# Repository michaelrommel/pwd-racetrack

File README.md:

# pwd-racetrack
A Pinewood Derby racetrack timer and start gate electronics circuits + firmware.

This software implements the firmware for a Pinewood Derby race track
electronics. The race track receives commands, like the setup or start commands
and sends back results, like the finishing times for each lane after a heat ends.

The racetrack electronics in the subdirectory circuits consists of three main parts:
- the main controller based on an Arduino Due with a protoype extension board.
  The extension board implements the connections to the finish line display
  modules and to the start gate.
- the display modules (one per lane) implement the main display of the achieved
  place in the heat and the display of the time in milliseconds. Also the LDR
  (Light Dependent Resistor) needed to detect the interruption of the laser
  beam is implemented on this module.
- the start gate electronics. This part is a separate Arduino Mega 2560
  controlling four RFID readers to detect the cars on each track, four OLED
  displays to shoe the car owner names and the solenoid for opening the start
  gate.

If you commit to this repo, please use descriptive commit messages. A good guide
can be found at: https://chris.beams.io/posts/git-commit/

In short, a properly formed Git commit subject line should always be able to 7
complete the following sentence:

- If applied, this commit will <_your subject line here_>

(c) 2018 by Michael Rommel

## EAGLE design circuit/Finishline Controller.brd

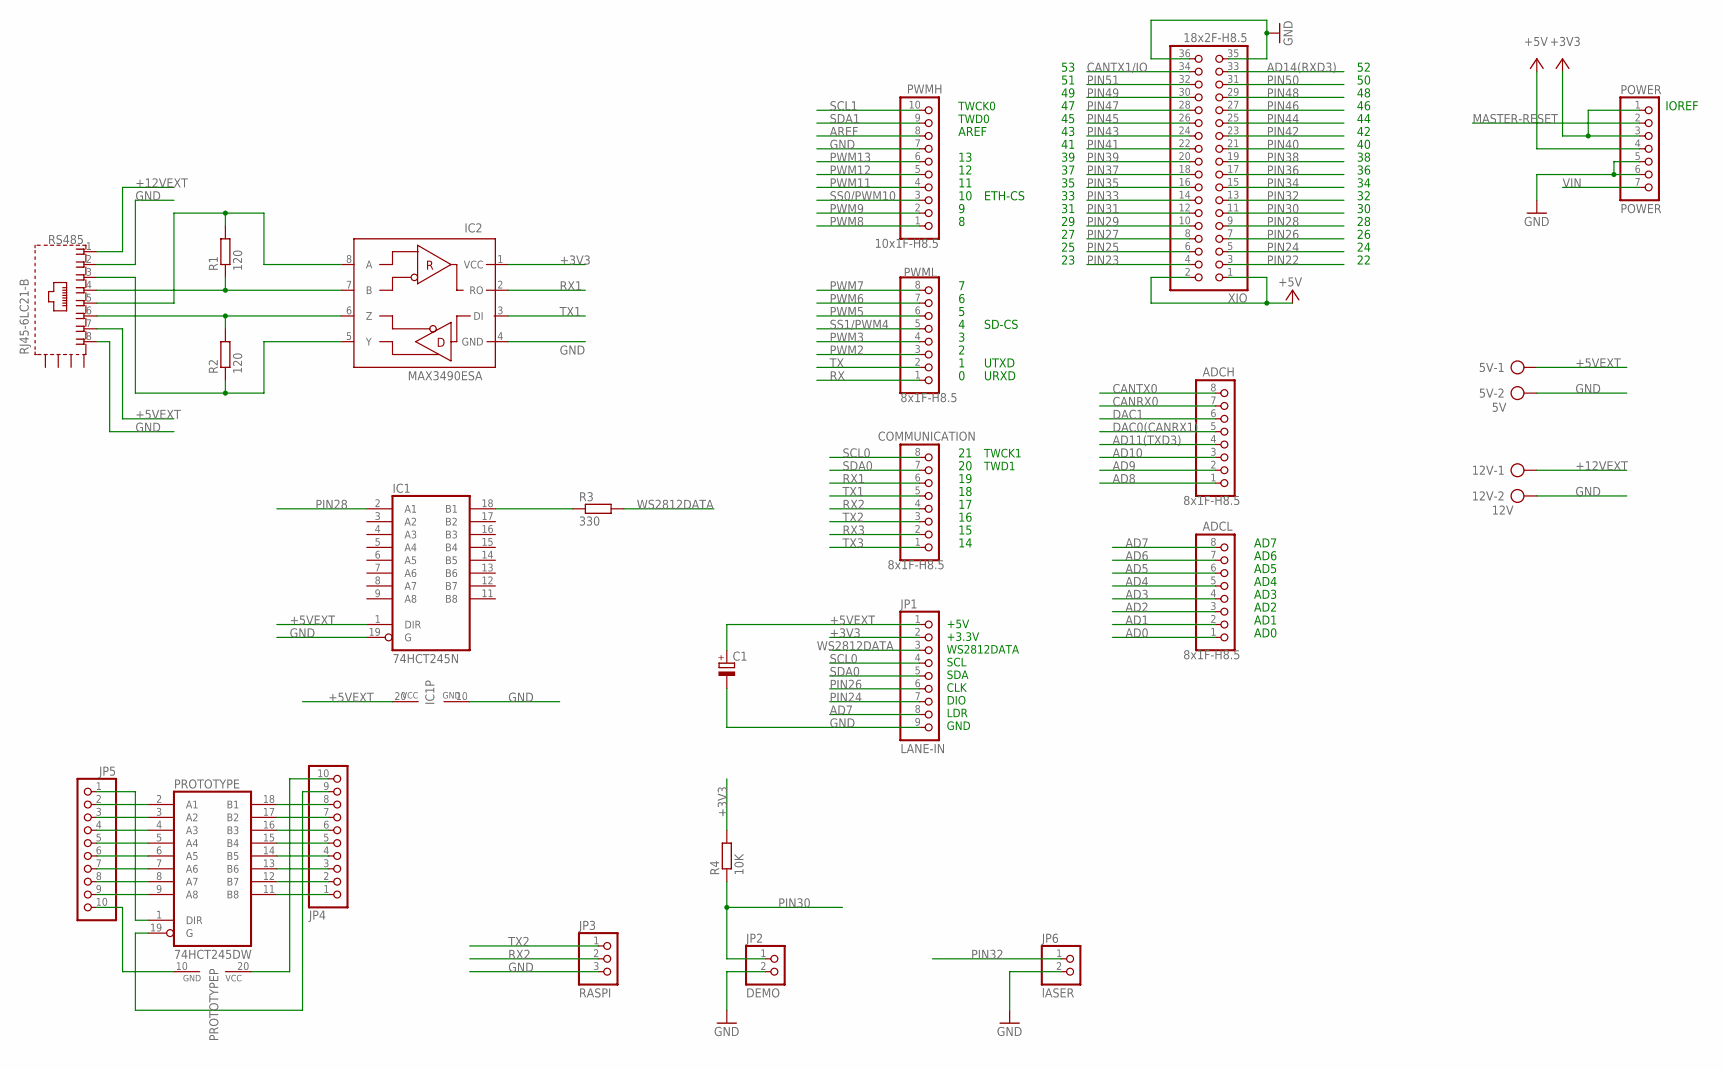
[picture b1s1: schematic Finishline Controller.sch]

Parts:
5V: 5V; AK300/2
12V: 12V; AK300/2
ADCH: 8x1F-H8.5; 1X08
ADCL: 8x1F-H8.5; 1X08
C1: CPOL-EUE5-10.5; E5-10,5
COMMUNICATION: 8x1F-H8.5; 1X08
IC1: 74HCT245N; DIL20
IC2: MAX3490ESA; SO08
JP1: LANE-IN; 1X09
JP2: DEMO; 1X02
JP3: RASPI; 1X03
JP4, JP5: PINHD-1X10; 1X10
JP6: lASER; 1X02
POWER: POWER; 1X07
PROTOTYPE: 74HCT245DW; SO20W
PWMH: 10x1F-H8.5; 1X10
PWML: 8x1F-H8.5; 1X08
R1, R2: 120; R0805
R3: 330; R0805
R4: 10K; R0805
RS485: RJ45-6LC21-B; RJ45-SHIELD1
XIO: 18x2F-H8.5; 2X18

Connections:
+3V3: IC2.1 (VCC), JP1.2, POWER.1, POWER.3, R4.2
+5V: POWER.4, XIO.1, XIO.2
+5VEXT: 5V.1, C1.+, IC1.1 (DIR), IC1.20 (VCC), JP1.1, RS485.7
+12VEXT: 12V.1, RS485.1
AD0: ADCL.1
AD1: ADCL.2
AD2: ADCL.3
AD3: ADCL.4
AD4: ADCL.5
AD5: ADCL.6
AD6: ADCL.7
AD7: ADCL.8, JP1.8
AD8: ADCH.1
AD9: ADCH.2
AD10: ADCH.3
AD11(TXD3): ADCH.4
AD14(RXD3): XIO.33
AREF: PWMH.8
CANRX0: ADCH.7
CANTX0: ADCH.8
CANTX1/IO: XIO.34
DAC0(CANRX1): ADCH.5
DAC1: ADCH.6
GND: 5V.2, 12V.2, C1.-, IC1.10 (GND), IC1.19 (G), IC2.4 (GND), JP1.9, JP2.2, JP3.3, JP6.2, POWER.5, POWER.6, PWMH.7, RS485.2, RS485.8, XIO.35, XIO.36
MASTER-RESET: POWER.2
unnamed: IC1.18 (B1), R3.1
unnamed: IC2.7 (B), R1.1, RS485.4
unnamed: IC2.6 (Z), R2.2, RS485.6
unnamed: IC2.5 (Y), R2.1, RS485.3
unnamed: IC2.8 (A), R1.2, RS485.5
unnamed: JP5.2, PROTOTYPE.2 (A1)
unnamed: JP5.3, PROTOTYPE.3 (A2)
unnamed: JP5.4, PROTOTYPE.4 (A3)
unnamed: JP5.5, PROTOTYPE.5 (A4)
unnamed: JP5.6, PROTOTYPE.6 (A5)
unnamed: JP5.7, PROTOTYPE.7 (A6)
unnamed: JP5.8, PROTOTYPE.8 (A7)
unnamed: JP5.9, PROTOTYPE.9 (A8)
unnamed: JP5.10, PROTOTYPE.10 (GND)
unnamed: JP5.1, PROTOTYPE.1 (DIR)
unnamed: JP4.8, PROTOTYPE.18 (B1)
unnamed: JP4.7, PROTOTYPE.17 (B2)
unnamed: JP4.6, PROTOTYPE.16 (B3)
unnamed: JP4.5, PROTOTYPE.15 (B4)
unnamed: JP4.4, PROTOTYPE.14 (B5)
unnamed: JP4.3, PROTOTYPE.13 (B6)
unnamed: JP4.2, PROTOTYPE.12 (B7)
unnamed: JP4.1, PROTOTYPE.11 (B8)
unnamed: JP4.9, PROTOTYPE.19 (G)
unnamed: JP4.10, PROTOTYPE.20 (VCC)
PIN22: XIO.3
PIN23: XIO.4
PIN24: JP1.7, XIO.5
PIN25: XIO.6
PIN26: JP1.6, XIO.7
PIN27: XIO.8
PIN28: IC1.2 (A1), XIO.9
PIN29: XIO.10
PIN30: JP2.1, R4.1, XIO.11
PIN31: XIO.12
PIN32: JP6.1, XIO.13
PIN33: XIO.14
PIN34: XIO.15
PIN35: XIO.16
PIN36: XIO.17
PIN37: XIO.18
PIN38: XIO.19
PIN39: XIO.20
PIN40: XIO.21
PIN41: XIO.22
PIN42: XIO.23
PIN43: XIO.24
PIN44: XIO.25
PIN45: XIO.26
PIN46: XIO.27
PIN47: XIO.28
PIN48: XIO.29
PIN49: XIO.30
PIN50: XIO.31
PIN51: XIO.32
PWM2: PWML.3
PWM3: PWML.4
PWM5: PWML.6
PWM6: PWML.7
PWM7: PWML.8
PWM8: PWMH.1
PWM9: PWMH.2
PWM11: PWMH.4
PWM12: PWMH.5
PWM13: PWMH.6
RX: PWML.1
RX1: COMMUNICATION.6, IC2.2 (RO)
RX2: COMMUNICATION.4, JP3.2
RX3: COMMUNICATION.2
SCL0: COMMUNICATION.8, JP1.4
SCL1: PWMH.10
SDA0: COMMUNICATION.7, JP1.5
SDA1: PWMH.9
SS0/PWM10: PWMH.3
SS1/PWM4: PWML.5
TX: PWML.2
TX1: COMMUNICATION.5, IC2.3 (DI)
TX2: COMMUNICATION.3, JP3.1
TX3: COMMUNICATION.1
VIN: POWER.7
WS2812DATA: JP1.3, R3.2

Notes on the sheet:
TWCK1
TWD1
IOREF
TWCK0
TWD0
AD1
AD2
AD3
AD4
AD5
AD6
AD0
AREF
AD7
SD-CS
UTXD
URXD
ETH-CS
+5V +3.3V WS2812DATA SCL SDA CLK DIO LDR GND

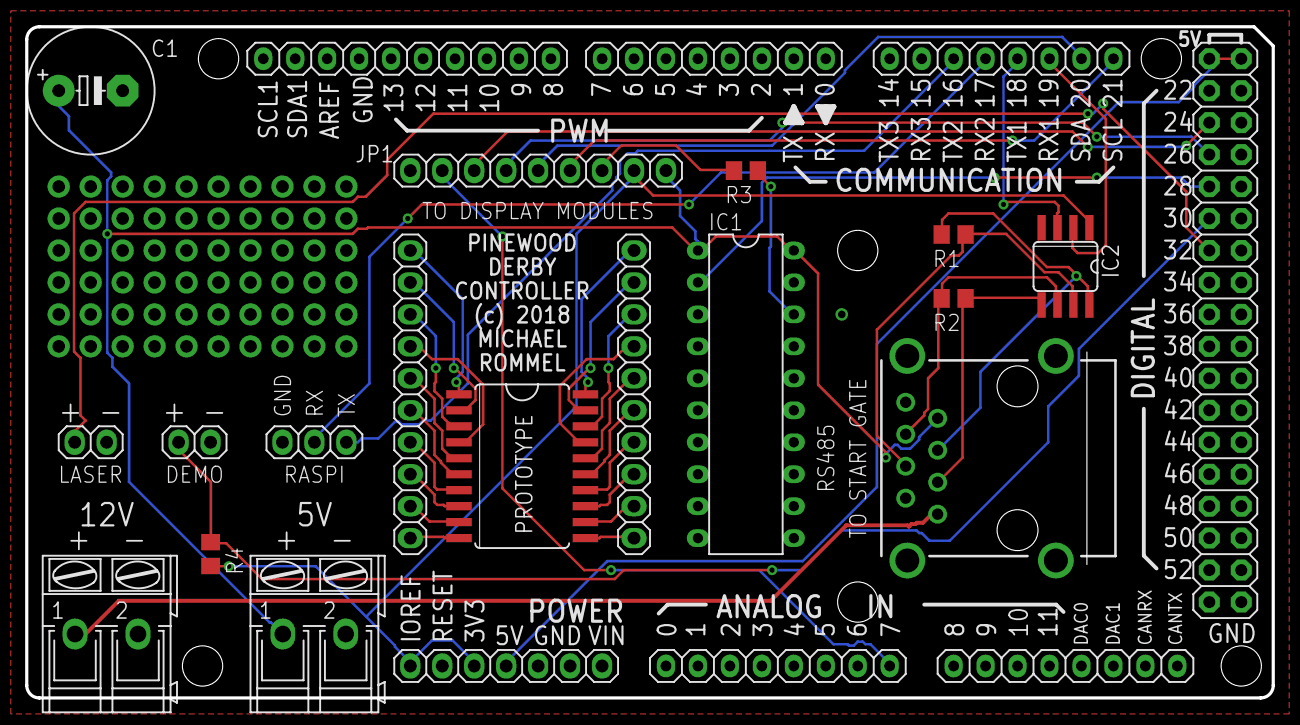
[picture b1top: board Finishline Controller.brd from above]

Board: 2 copper layers, 99.1 x 53.3 mm, 24 parts (0 on the bottom side), 43 nets.

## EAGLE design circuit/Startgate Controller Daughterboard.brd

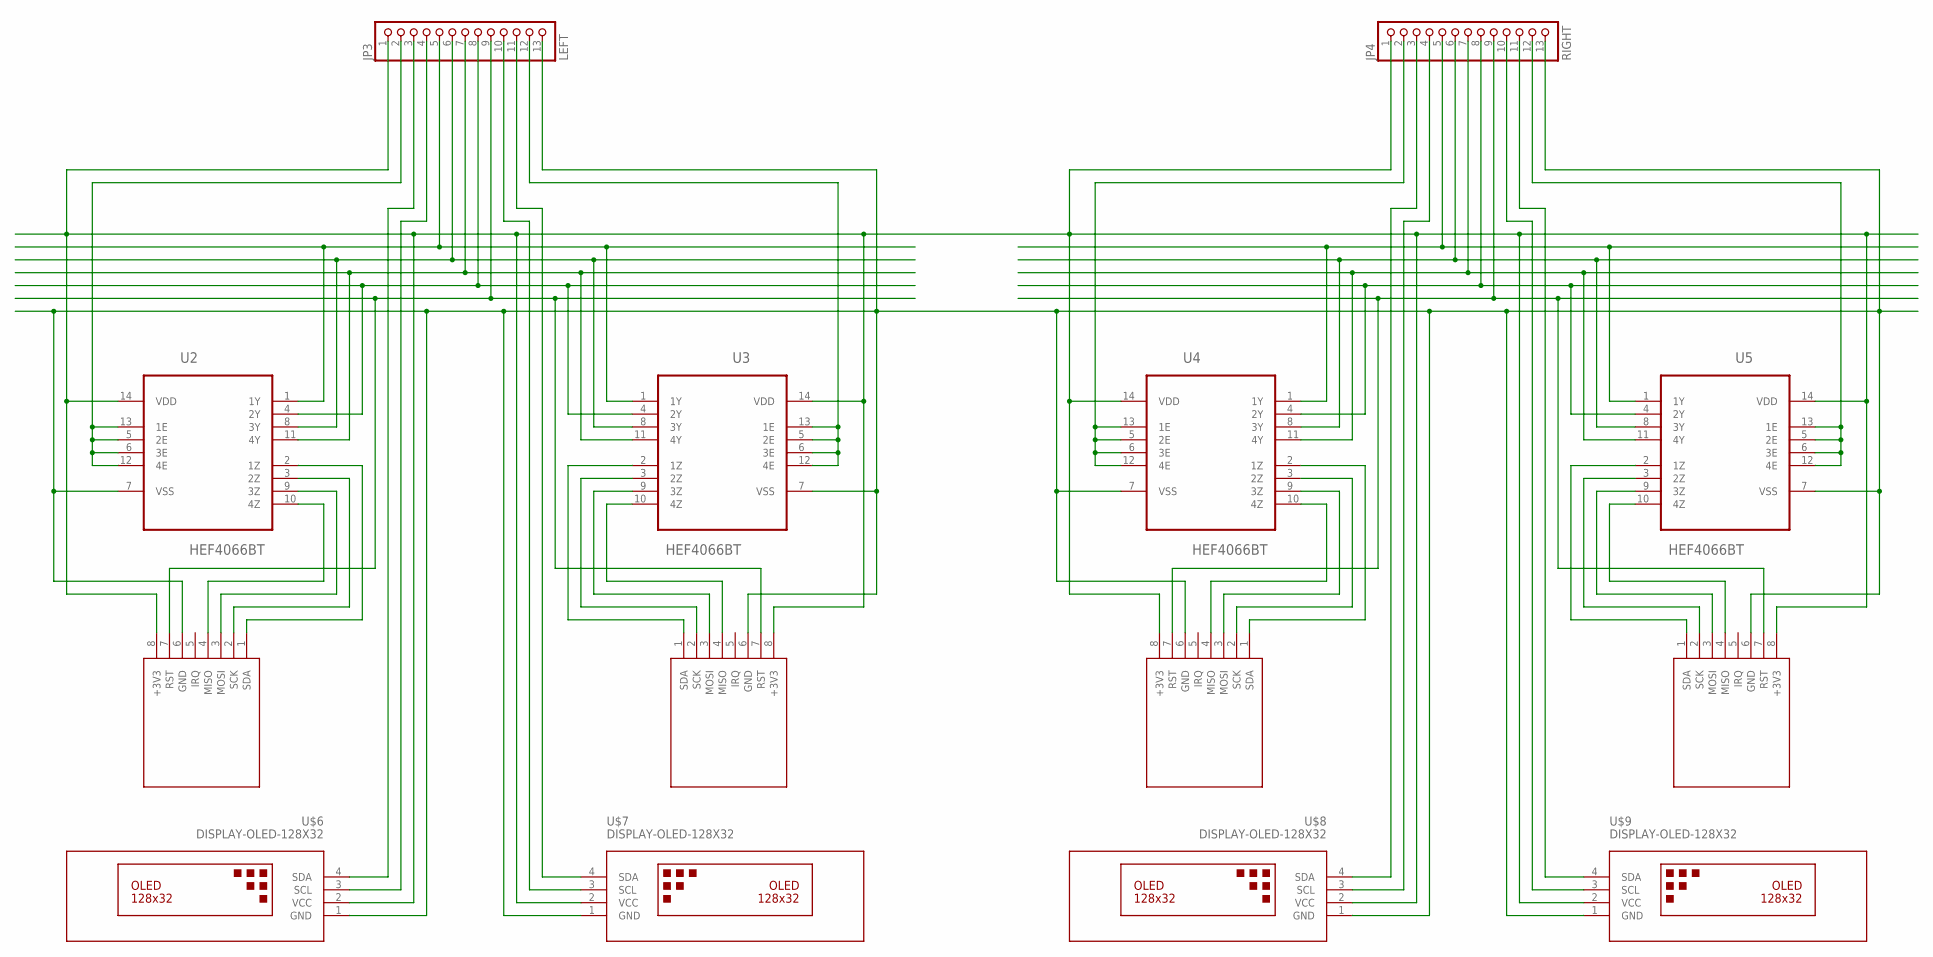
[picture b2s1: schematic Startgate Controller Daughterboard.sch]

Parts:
JP3: LEFT; 1X13
JP4: RIGHT; 1X13
U2, U3, U4, U5: HEF4066BT; SOIC127P600X175-14N
U$2, U$3, U$4, U$5: RFID-RC522
U$6, U$7, U$8, U$9: DISPLAY-OLED-128X32

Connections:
+3V3: JP3.1, JP4.1, U2.14 (VDD), U3.14 (VDD), U4.14 (VDD), U5.14 (VDD), U$2.8 (+3V3), U$3.8 (+3V3), U$4.8 (+3V3), U$5.8 (+3V3), U$6.2 (VCC), U$7.2 (VCC), U$8.2 (VCC), U$9.2 (VCC)
ENA1: JP3.2, U2.5 (2E), U2.6 (3E), U2.12 (4E), U2.13 (1E)
ENA2: JP3.12, U3.5 (2E), U3.6 (3E), U3.12 (4E), U3.13 (1E)
ENA3: JP4.2, U4.5 (2E), U4.6 (3E), U4.12 (4E), U4.13 (1E)
GND: JP3.13, JP4.13, U2.7 (VSS), U3.7 (VSS), U4.7 (VSS), U5.7 (VSS), U$2.6 (GND), U$3.6 (GND), U$4.6 (GND), U$5.6 (GND), U$6.1 (GND), U$7.1 (GND), U$8.1 (GND), U$9.1 (GND)
MISO: JP4.7, U4.11 (4Y), U5.11 (4Y)
MISO-OUT1: U2.10 (4Z), U$2.4 (MISO)
MISO-OUT2: U3.10 (4Z), U$3.4 (MISO)
MISO-OUT3: U4.10 (4Z), U$4.4 (MISO)
MISO-OUT4: U5.10 (4Z), U$5.4 (MISO)
MOSI: JP4.6, U4.8 (3Y), U5.8 (3Y)
MOSI-OUT1: U2.9 (3Z), U$2.3 (MOSI)
MOSI-OUT2: U3.9 (3Z), U$3.3 (MOSI)
MOSI-OUT3: U4.9 (3Z), U$4.3 (MOSI)
MOSI-OUT4: U5.9 (3Z), U$5.3 (MOSI)
unnamed: JP3.6, U2.8 (3Y), U3.8 (3Y)
unnamed: JP3.5, U2.1 (1Y), U3.1 (1Y)
unnamed: JP3.7, U2.11 (4Y), U3.11 (4Y)
unnamed: JP3.8, U2.4 (2Y), U3.4 (2Y)
unnamed: JP4.12, U5.5 (2E), U5.6 (3E), U5.12 (4E), U5.13 (1E)
RST: JP3.9, JP4.9, U$2.7 (RST), U$3.7 (RST), U$4.7 (RST), U$5.7 (RST)
SCK: JP4.8, U4.4 (2Y), U5.4 (2Y)
SCK-OUT1: U2.3 (2Z), U$2.2 (SCK)
SCK-OUT2: U3.3 (2Z), U$3.2 (SCK)
SCK-OUT3: U4.3 (2Z), U$4.2 (SCK)
SCK-OUT4: U5.3 (2Z), U$5.2 (SCK)
SCL1: JP3.4, U$6.3 (SCL)
SCL2: JP3.10, U$7.3 (SCL)
SCL3: JP4.4, U$8.3 (SCL)
SCL4: JP4.10, U$9.3 (SCL)
SDA1: JP3.3, U$6.4 (SDA)
SDA2: JP3.11, U$7.4 (SDA)
SDA3: JP4.3, U$8.4 (SDA)
SDA4: JP4.11, U$9.4 (SDA)
SS: JP4.5, U4.1 (1Y), U5.1 (1Y)
SS-OUT1: U2.2 (1Z), U$2.1 (SDA)
SS-OUT2: U3.2 (1Z), U$3.1 (SDA)
SS-OUT3: U4.2 (1Z), U$4.1 (SDA)
SS-OUT4: U5.2 (1Z), U$5.1 (SDA)

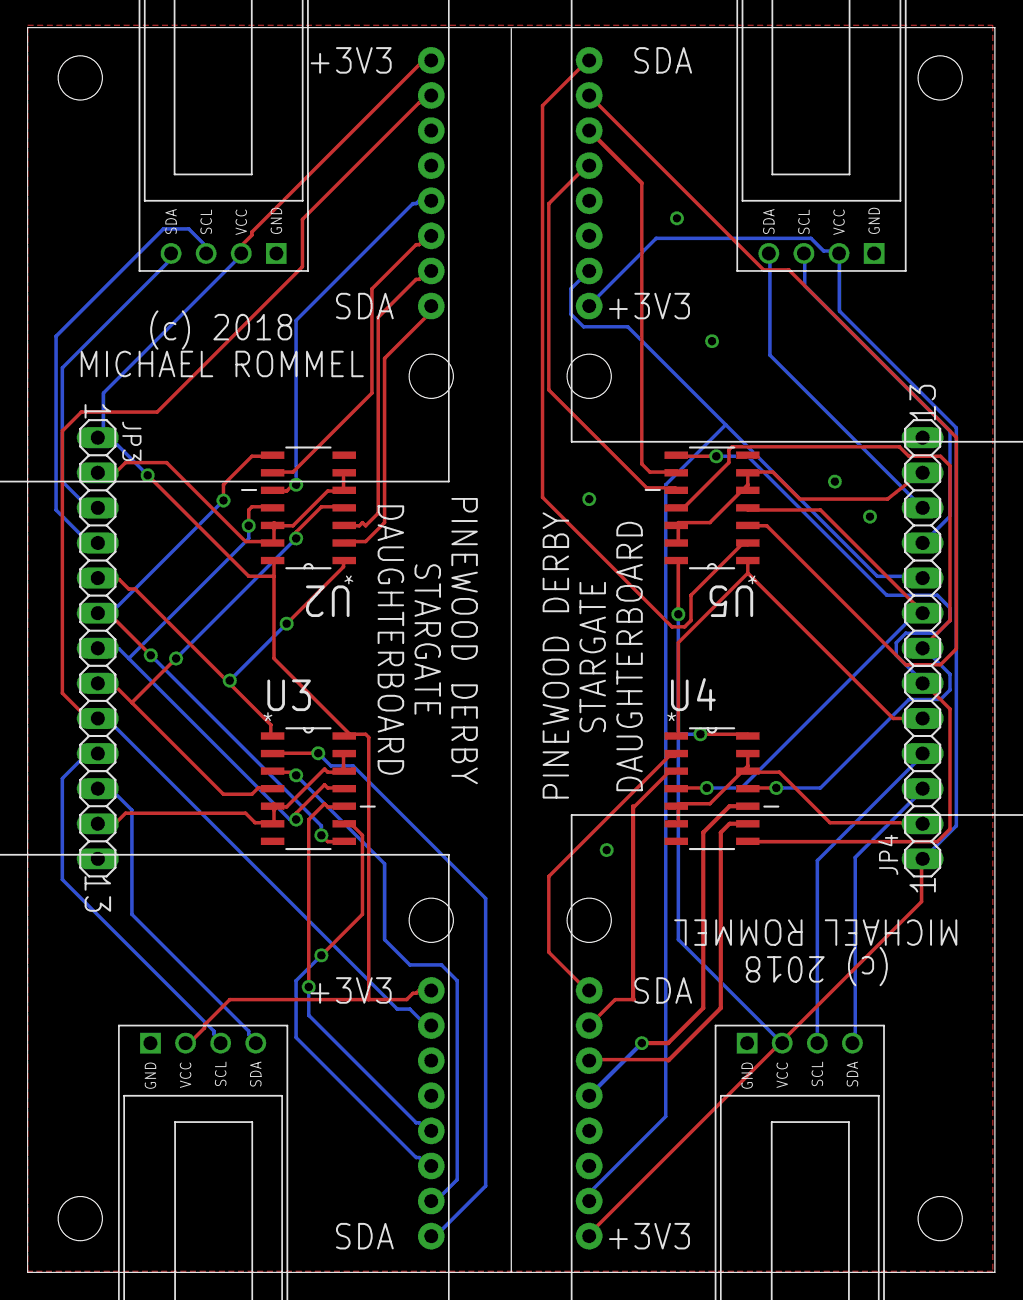
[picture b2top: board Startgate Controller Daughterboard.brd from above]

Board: 2 copper layers, 70.0 x 90.1 mm, 14 parts (0 on the bottom side), 39 nets.

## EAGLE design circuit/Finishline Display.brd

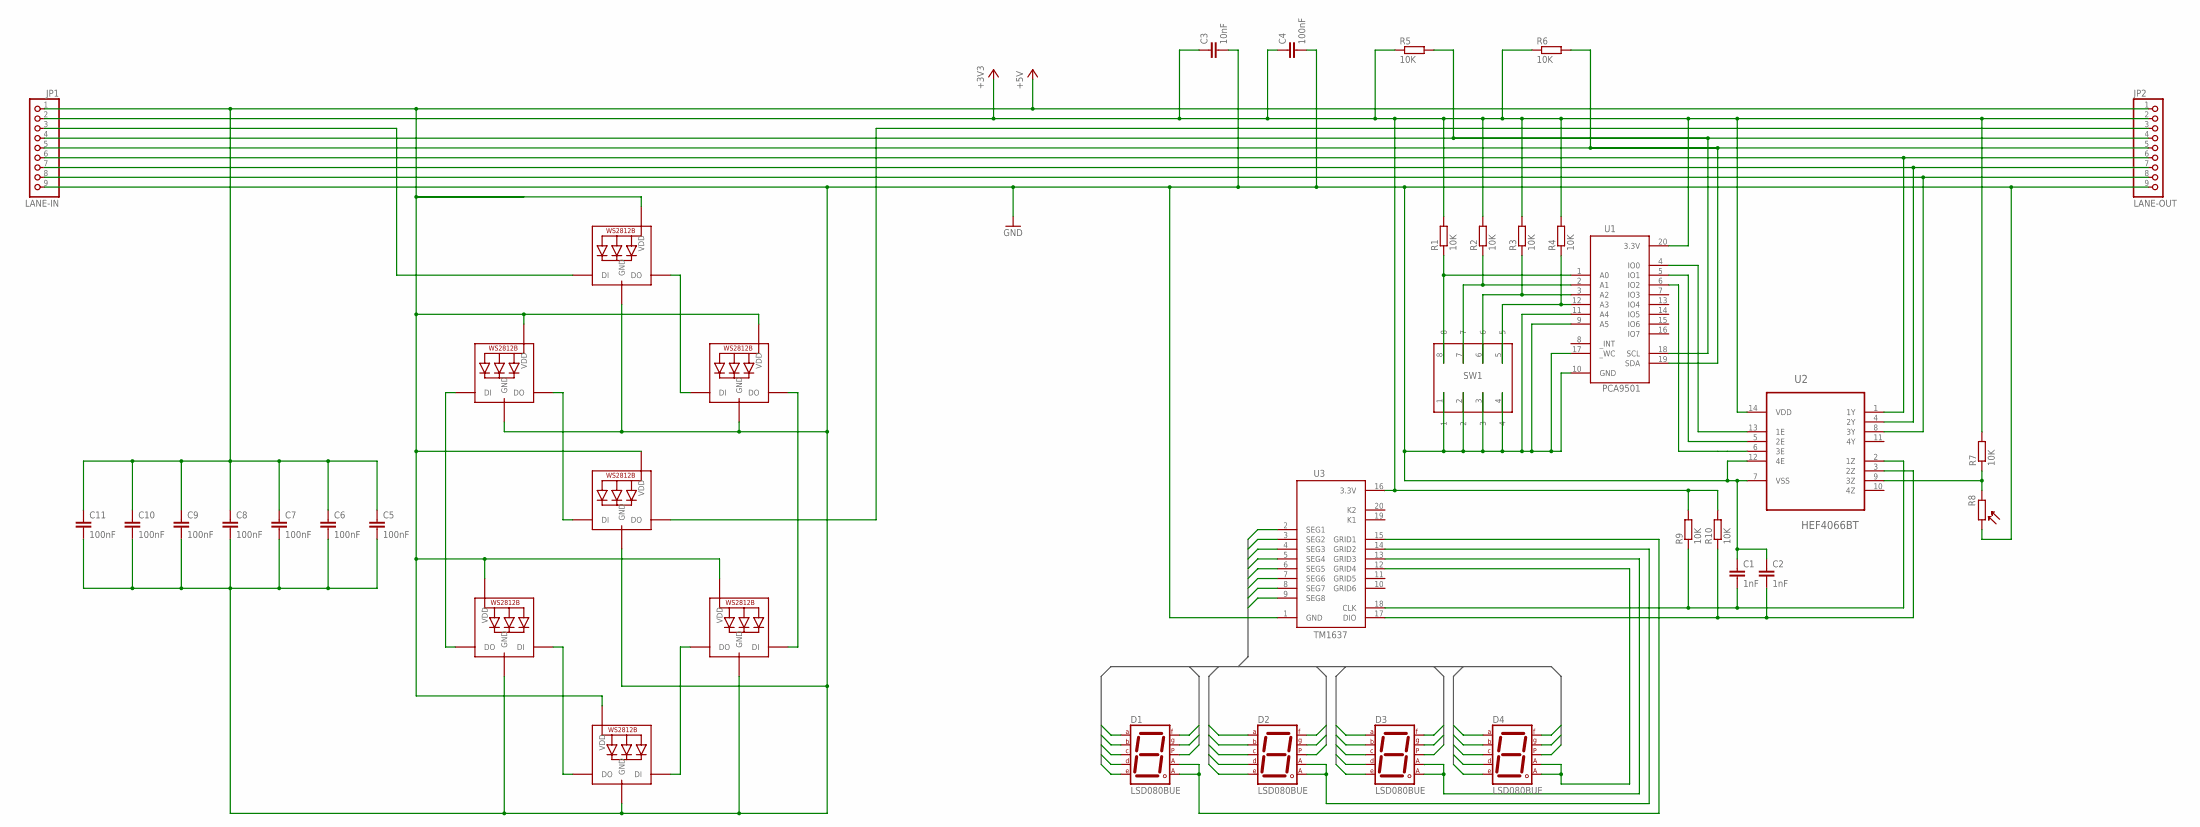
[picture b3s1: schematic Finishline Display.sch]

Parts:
C1, C2: 1nF; C0805
C3: 10nF; C0805
C4, C5, C6, C7, C8, C9, C10, C11: 100nF; C0805
D1, D2, D3, D4: LSD080BUE; 7SEG-13
JP1: LANE-IN; 1X09
JP2: LANE-OUT; 1X09
LED1, LED2, LED3, LED4, LED5, LED6, LED7: WS2812B5050; WS2812B
R1, R2, R3, R4, R5, R6, R7, R9, R10: 10K; M0805
R8: LDR 10K; 1X02
SW1: 416131160804
U1: PCA9501; SOIC127P1032X265-20N
U2: HEF4066BT; SOIC127P600X175-14N
U3: TM1637; SOIC127P1032X265-20N

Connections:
+3V3: C3.1, C4.1, JP1.2, JP2.2, R1.2, R2.2, R3.2, R4.2, R5.1, R6.1, R7.2, R9.2, R10.2, U1.20 (3.3V), U2.14 (VDD), U3.16 (3.3V)
+5V: C5.1, C6.1, C7.1, C8.1, C9.1, C10.1, C11.1, JP1.1, JP2.1, LED1.1-VDD (VDD), LED2.1-VDD (VDD), LED3.1-VDD (VDD), LED4.1-VDD (VDD), LED5.1-VDD (VDD), LED6.1-VDD (VDD), LED7.1-VDD (VDD)
CLK: JP1.6, JP2.6, U2.1 (1Y)
DIO: JP1.7, JP2.7, U2.4 (2Y)
GND: C1.1, C2.1, C3.2, C4.2, C5.2, C6.2, C7.2, C8.2, C9.2, C10.2, C11.2, JP1.9, JP2.9, LED1.3-GND (GND), LED2.3-GND (GND), LED3.3-GND (GND), LED4.3-GND (GND), LED5.3-GND (GND), LED6.3-GND (GND), LED7.3-GND (GND), R8.2, SW1.1, SW1.2, SW1.3, SW1.4, U1.9 (A5), U1.10 (GND), U1.11 (A4), U1.17 (_WC), U2.7 (VSS), U2.12 (4E), U3.1 (GND)
LDR: JP1.8, JP2.8, U2.8 (3Y)
unnamed: U1.4 (IO0), U2.13 (1E)
unnamed: LED1.2-DOUT (DO), LED2.4-DIN (DI)
unnamed: LED2.2-DOUT (DO), LED3.4-DIN (DI)
unnamed: LED3.2-DOUT (DO), LED4.4-DIN (DI)
unnamed: LED4.2-DOUT (DO), LED5.4-DIN (DI)
unnamed: LED5.2-DOUT (DO), LED6.4-DIN (DI)
unnamed: LED6.2-DOUT (DO), LED7.4-DIN (DI)
unnamed: JP2.3, LED7.2-DOUT (DO)
unnamed: D1.3 (CA1), D1.8 (CA2), U3.15 (GRID1)
unnamed: D2.3 (CA1), D2.8 (CA2), U3.14 (GRID2)
unnamed: D3.3 (CA1), D3.8 (CA2), U3.13 (GRID3)
unnamed: D4.3 (CA1), D4.8 (CA2), U3.12 (GRID4)
unnamed: U1.5 (IO1), U2.5 (2E)
unnamed: R1.1, SW1.8, U1.1 (A0)
unnamed: R2.1, SW1.7, U1.2 (A1)
unnamed: R3.1, SW1.6, U1.3 (A2)
unnamed: R4.1, SW1.5, U1.12 (A3)
unnamed: C1.2, R9.1, U2.2 (1Z), U3.18 (CLK)
unnamed: C2.2, R10.1, U2.3 (2Z), U3.17 (DIO)
unnamed: R7.1, R8.1, U2.9 (3Z)
unnamed: U1.6 (IO2), U2.6 (3E)
SCL: JP1.4, JP2.4, R5.2, U1.18 (SCL)
SDA: JP1.5, JP2.5, R6.2, U1.19 (SDA)
SEG1: D1.7 (A), D2.7 (A), D3.7 (A), D4.7 (A), U3.2 (SEG1)
SEG2: D1.6 (B), D2.6 (B), D3.6 (B), D4.6 (B), U3.3 (SEG2)
SEG3: D1.4 (C), D2.4 (C), D3.4 (C), D4.4 (C), U3.4 (SEG3)
SEG4: D1.2 (D), D2.2 (D), D3.2 (D), D4.2 (D), U3.5 (SEG4)
SEG5: D1.1 (E), D2.1 (E), D3.1 (E), D4.1 (E), U3.6 (SEG5)
SEG6: D1.9 (F), D2.9 (F), D3.9 (F), D4.9 (F), U3.7 (SEG6)
SEG7: D1.10 (G), D2.10 (G), D3.10 (G), D4.10 (G), U3.8 (SEG7)
SEG8: D1.5 (DP), D2.5 (DP), D3.5 (DP), D4.5 (DP), U3.9 (SEG8)
WS2812DATA: JP1.3, LED1.4-DIN (DI)

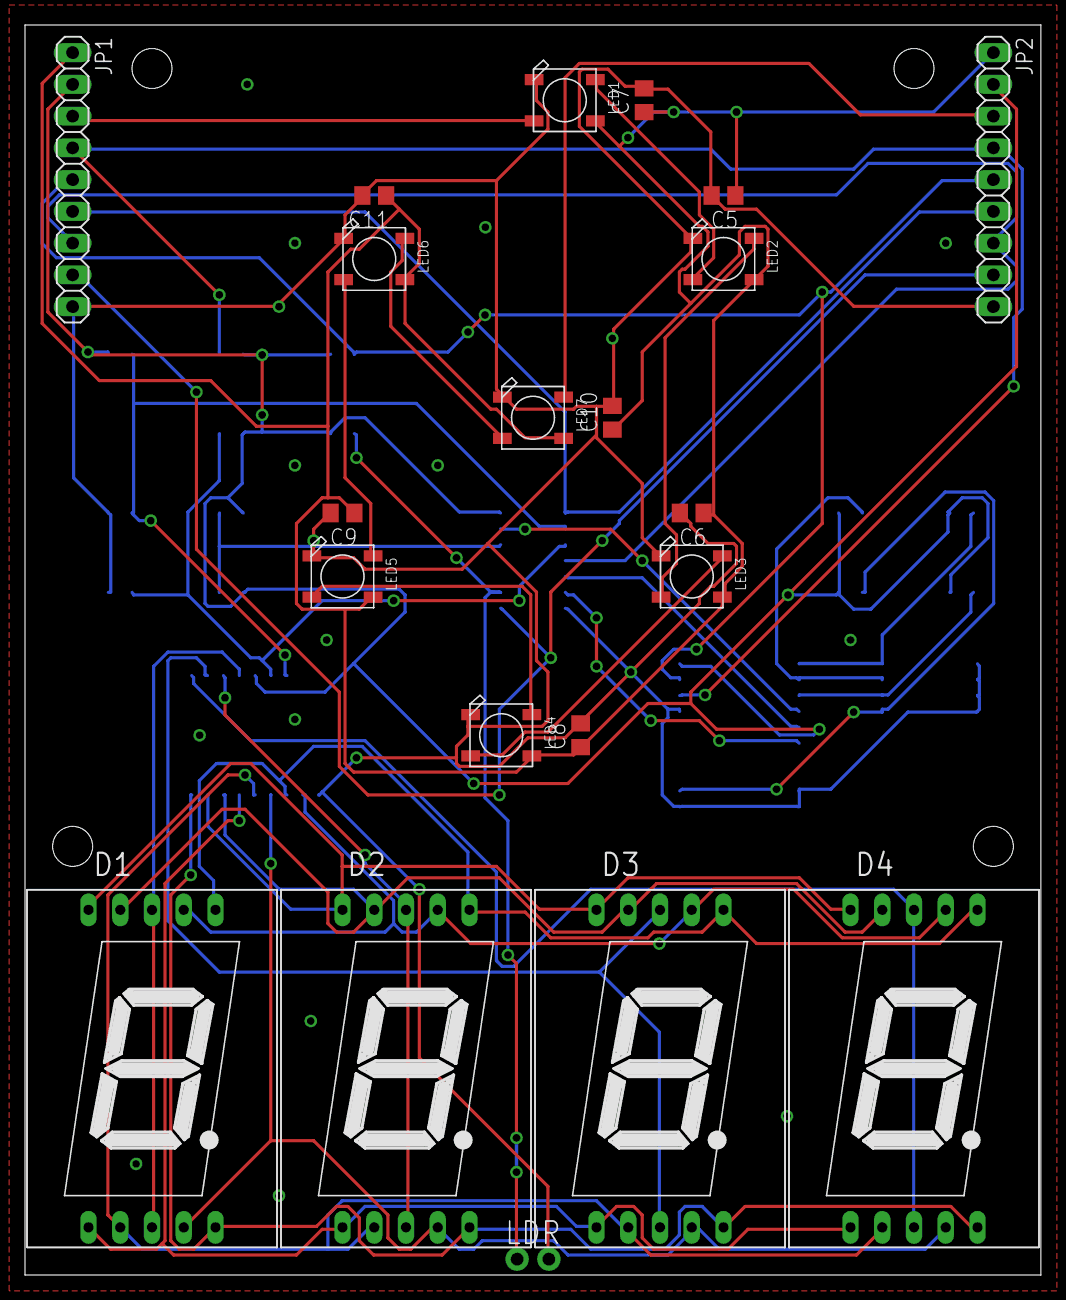
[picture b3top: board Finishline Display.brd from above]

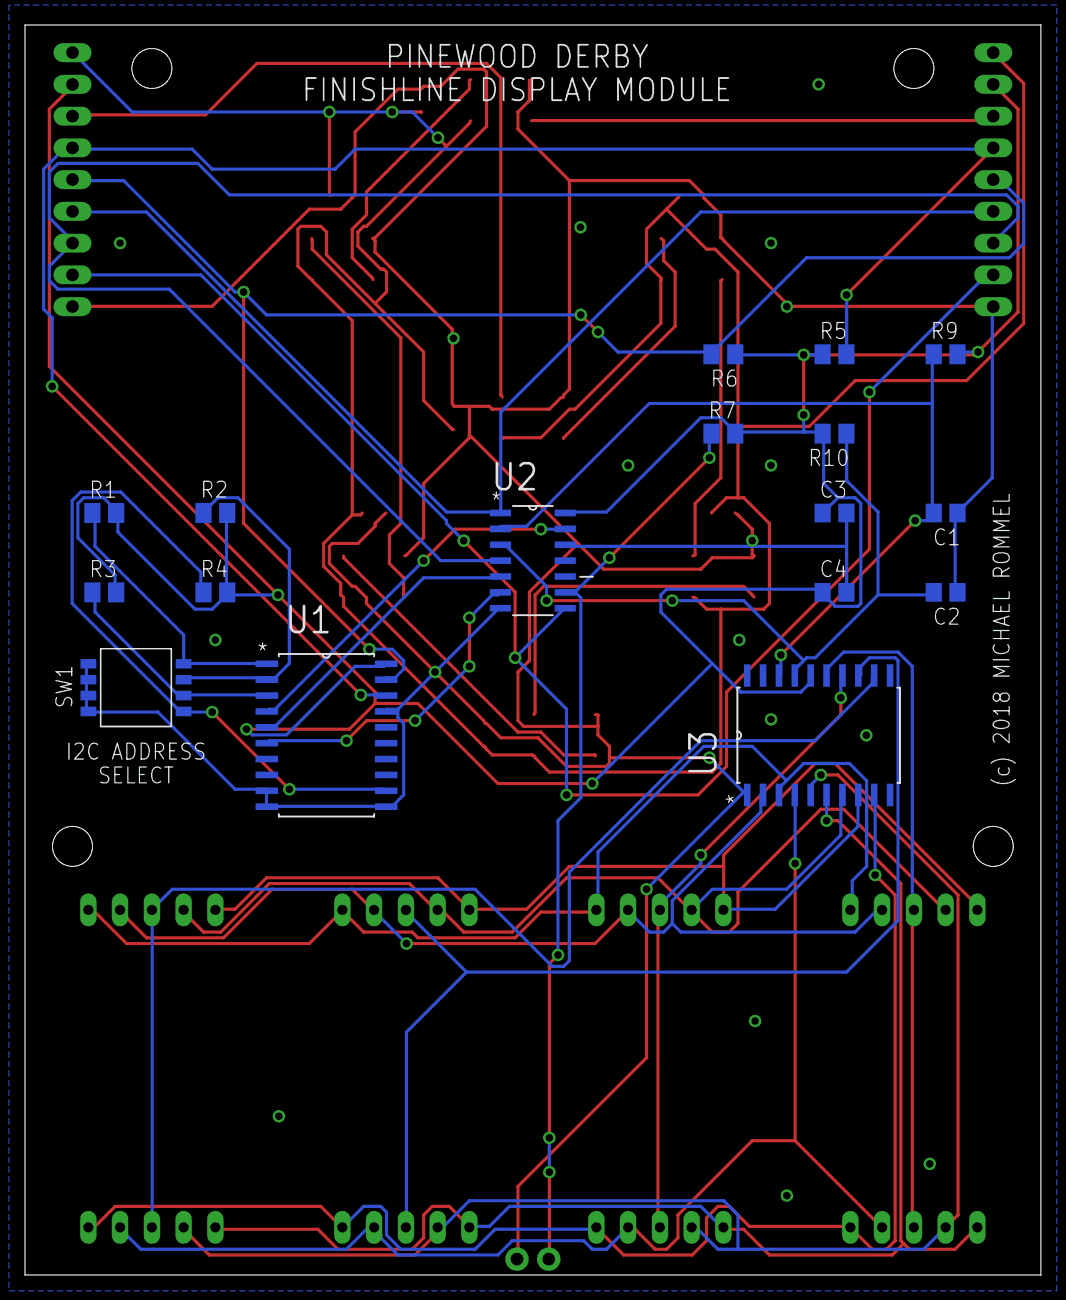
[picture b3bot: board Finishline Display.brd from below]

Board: 2 copper layers, 81.3 x 100.0 mm, 38 parts (17 on the bottom side), 38 nets.

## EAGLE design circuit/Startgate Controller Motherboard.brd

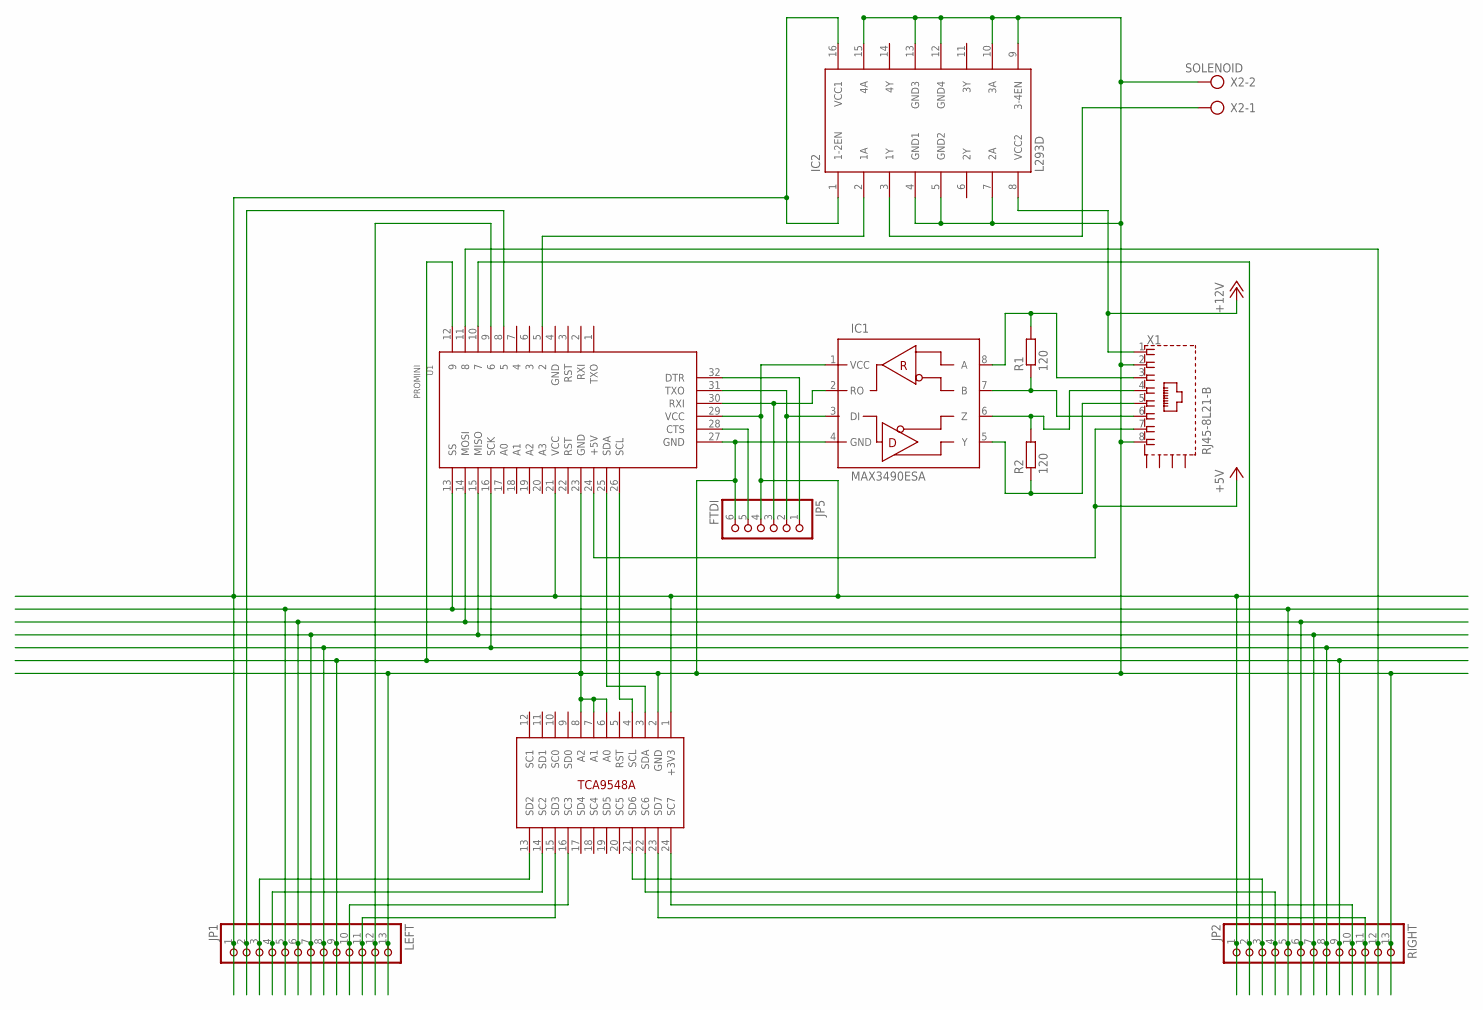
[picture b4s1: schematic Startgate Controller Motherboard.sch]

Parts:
IC1: MAX3490ESA; SO08
IC2: L293D; DIL16
JP1: LEFT; 1X13
JP2: RIGHT; 1X13
JP5: FTDI; 1X06
R1, R2: 120; R0805
U1: PROMINI; ARDUINOPROMINI
U2: TCA9548A; DIL24
X1: RJ45-8L21-B; RJ45-SHIELD1
X2: SOLENOID; AK300/2

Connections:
+3V3: IC1.1 (VCC), IC2.1 (1-2EN), IC2.16 (VCC1), JP1.1, JP2.1, JP5.4, U1.21 (VCC), U1.29 (VCC), U2.1 (+3V3)
+5V: U1.24 (+5V), X1.7
+12V: IC2.8 (VCC2), X1.1
ENA1: JP1.2, U1.8 (5)
ENA2: JP1.12, U1.9 (6)
ENA3: JP2.2, U1.10 (7)
ENA4: JP2.12, U1.11 (8)
GND: IC1.4 (GND), IC2.4 (GND1), IC2.5 (GND2), IC2.7 (2A), IC2.9 (3-4EN), IC2.10 (3A), IC2.12 (GND4), IC2.13 (GND3), IC2.15 (4A), JP1.13, JP2.13, JP5.6, U1.23 (GND), U1.27 (GND), U2.2 (GND), U2.6 (A0), U2.7 (A1), U2.8 (A2), X1.2, X1.8, X2.2
MISO: JP1.7, JP2.7, U1.15 (MISO)
MOSI: JP1.6, JP2.6, U1.14 (MOSI)
unnamed: IC1.3 (DI), JP5.2, U1.31 (TXO)
unnamed: IC1.2 (RO), JP5.3, U1.30 (RXI)
unnamed: IC1.8 (A), R1.2, X1.3
unnamed: IC1.7 (B), R1.1, X1.6
unnamed: U1.26 (SCL), U2.4 (SCL)
unnamed: U1.25 (SDA), U2.3 (SDA)
unnamed: IC1.5 (Y), R2.1, X1.5
unnamed: IC1.6 (Z), R2.2, X1.4
unnamed: JP5.1, U1.32 (DTR)
unnamed: IC2.2 (1A), U1.5 (2)
unnamed: IC2.3 (1Y), X2.1
unnamed: JP5.5, U1.28 (CTS)
RST: JP1.9, JP2.9, U1.12 (9)
SCK: JP1.8, JP2.8, U1.16 (SCK)
SCL1: JP1.4, U2.14 (SC2)
SCL2: JP1.10, U2.16 (SC3)
SCL3: JP2.4, U2.22 (SC6)
SCL4: JP2.10, U2.24 (SC7)
SDA1: JP1.3, U2.13 (SD2)
SDA2: JP1.11, U2.15 (SD3)
SDA3: JP2.3, U2.21 (SD6)
SDA4: JP2.11, U2.23 (SD7)
SS: JP1.5, JP2.5, U1.13 (SS)

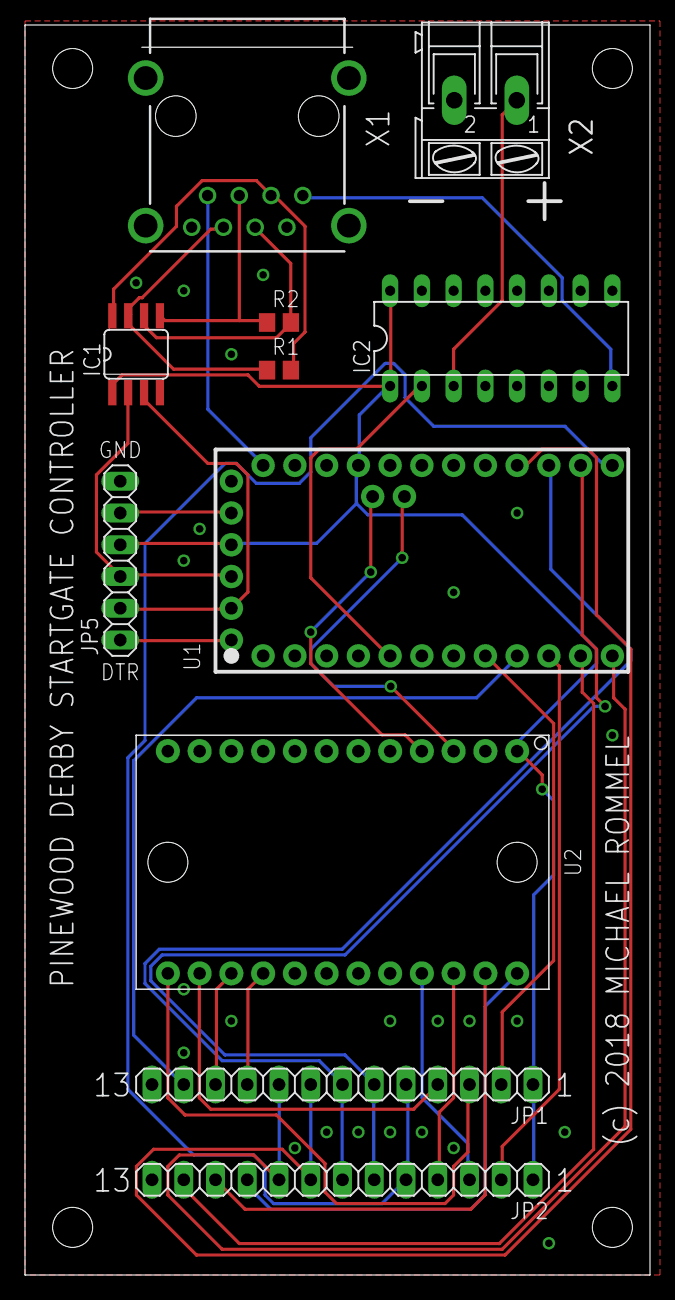
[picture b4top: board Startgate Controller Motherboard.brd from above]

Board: 2 copper layers, 50.0 x 100.0 mm, 11 parts (0 on the bottom side), 33 nets.

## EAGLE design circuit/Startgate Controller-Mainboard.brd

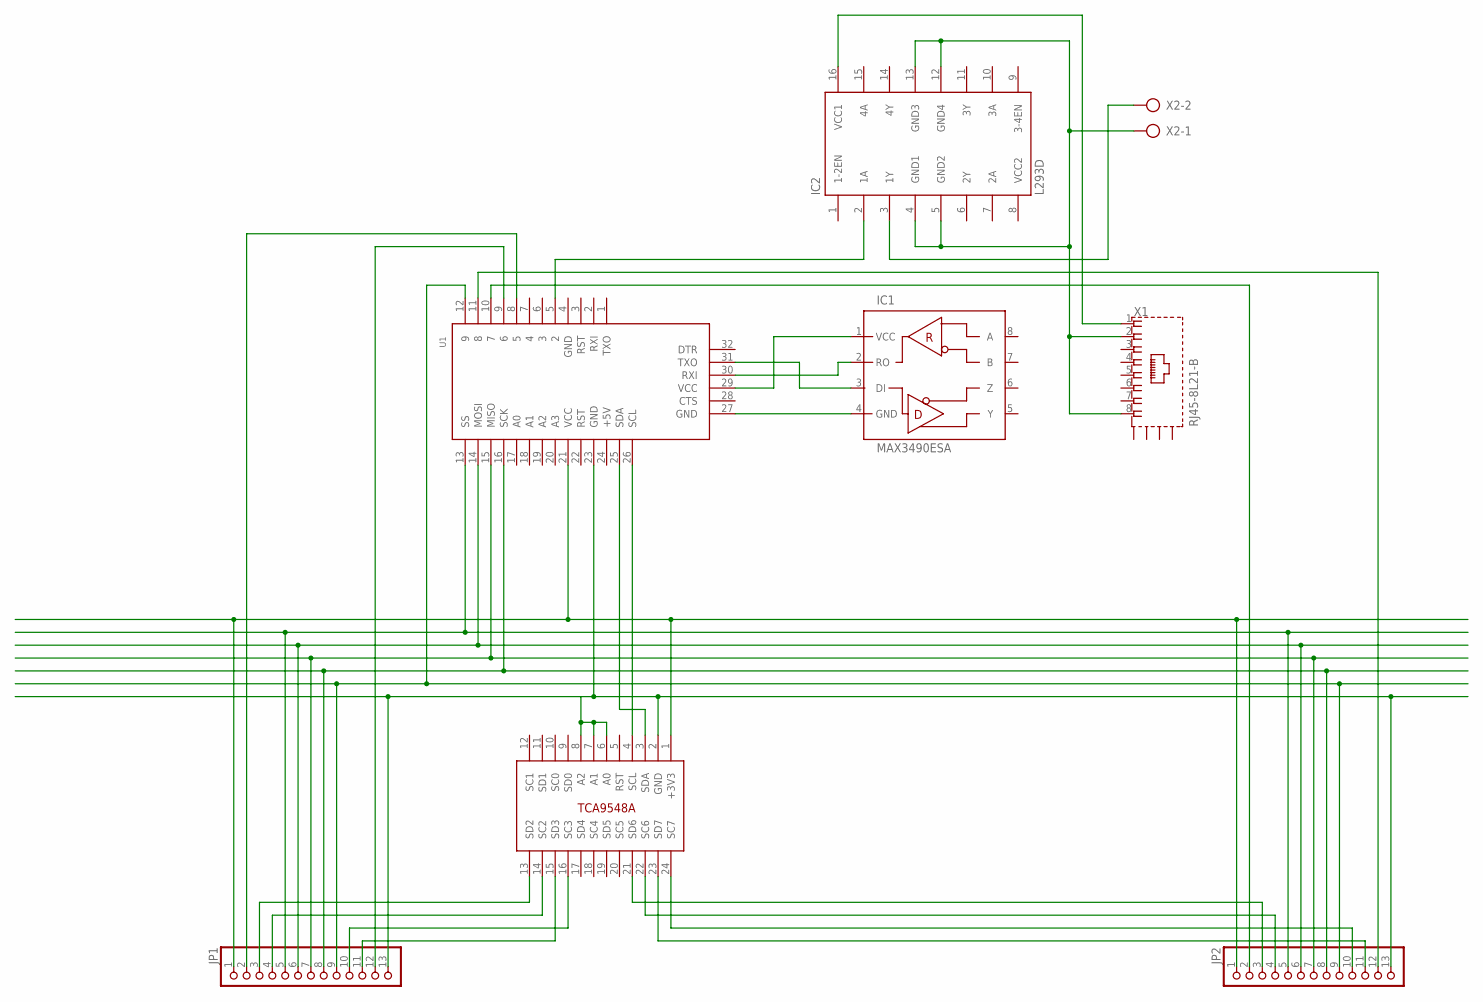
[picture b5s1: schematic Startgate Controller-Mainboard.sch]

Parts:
IC1: MAX3490ESA; SO08
IC2: L293D; DIL16
JP1, JP2: PINHD-1X13; 1X13
U1: ARDUINOPROMINI
U$1: TCA9548A; DIL24
X1: RJ45-8L21-B; RJ45-SHIELD1
X2: AK300/2

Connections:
+3V3: IC1.1 (VCC), JP1.1, JP2.1, U1.21 (VCC), U1.29 (VCC), U$1.1 (+3V3)
+5V: U1.24 (+5V)
ENA1: JP1.2, U1.8 (5)
ENA2: JP1.12, U1.9 (6)
ENA3: JP2.2, U1.10 (7)
ENA4: JP2.12, U1.11 (8)
GND: IC1.4 (GND), JP1.13, JP2.13, U1.23 (GND), U1.27 (GND), U$1.2 (GND), U$1.6 (A0), U$1.7 (A1), U$1.8 (A2)
MISO: JP1.7, JP2.7, U1.15 (MISO)
MOSI: JP1.6, JP2.6, U1.14 (MOSI)
unnamed: IC1.3 (DI), U1.31 (TXO)
unnamed: IC1.2 (RO), U1.30 (RXI)
unnamed: U1.26 (SCL), U$1.4 (SCL)
unnamed: U1.25 (SDA), U$1.3 (SDA)
unnamed: IC2.2 (1A), U1.5 (2)
unnamed: IC2.3 (1Y), X2.2
unnamed: IC2.16 (VCC1), X1.1
unnamed: IC2.4 (GND1), IC2.5 (GND2), IC2.12 (GND4), IC2.13 (GND3), X1.2, X1.8, X2.1
RST: JP1.9, JP2.9, U1.12 (9)
SCK: JP1.8, JP2.8, U1.16 (SCK)
SCL1: JP1.4, U$1.14 (SC2)
SCL2: JP1.10, U$1.16 (SC3)
SCL3: JP2.4, U$1.22 (SC6)
SCL4: JP2.10, U$1.24 (SC7)
SDA1: JP1.3, U$1.13 (SD2)
SDA2: JP1.11, U$1.15 (SD3)
SDA3: JP2.3, U$1.21 (SD6)
SDA4: JP2.11, U$1.23 (SD7)
SS: JP1.5, JP2.5, U1.13 (SS)
VCC2: IC2.8 (VCC2)

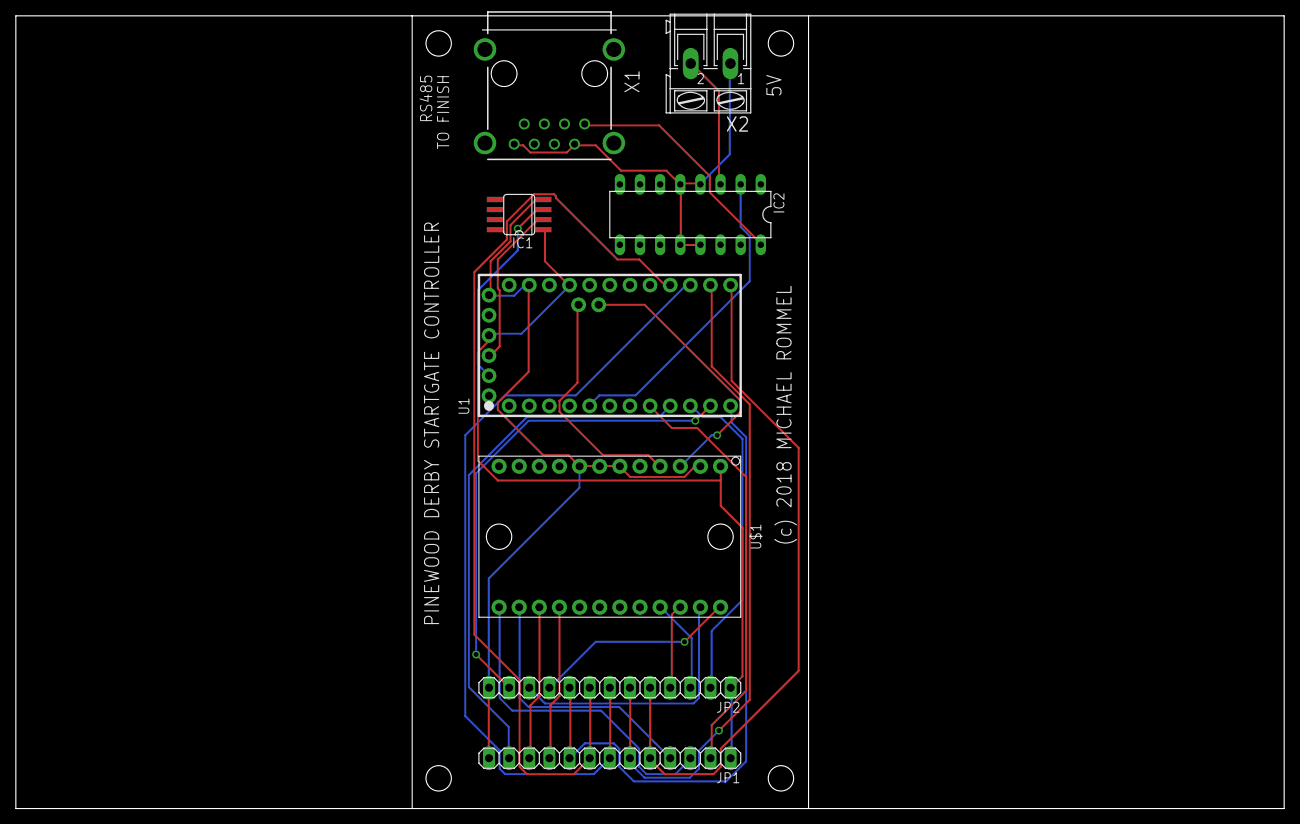
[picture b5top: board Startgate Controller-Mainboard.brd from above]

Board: 2 copper layers, 160.0 x 100.0 mm, 8 parts (0 on the bottom side), 27 nets.

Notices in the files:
circuit/Finishline Display.brd:
(c) 2018 MICHAEL ROMMEL
parts and their libraries:
Wurth_Elektronik_Electromechanic_Switchs: Copyright: Würth Elektronik
diy-modules: Released under the Creative Commons Attribution 4.0 International License: http://creativecommons.org/licenses/by/4.0
